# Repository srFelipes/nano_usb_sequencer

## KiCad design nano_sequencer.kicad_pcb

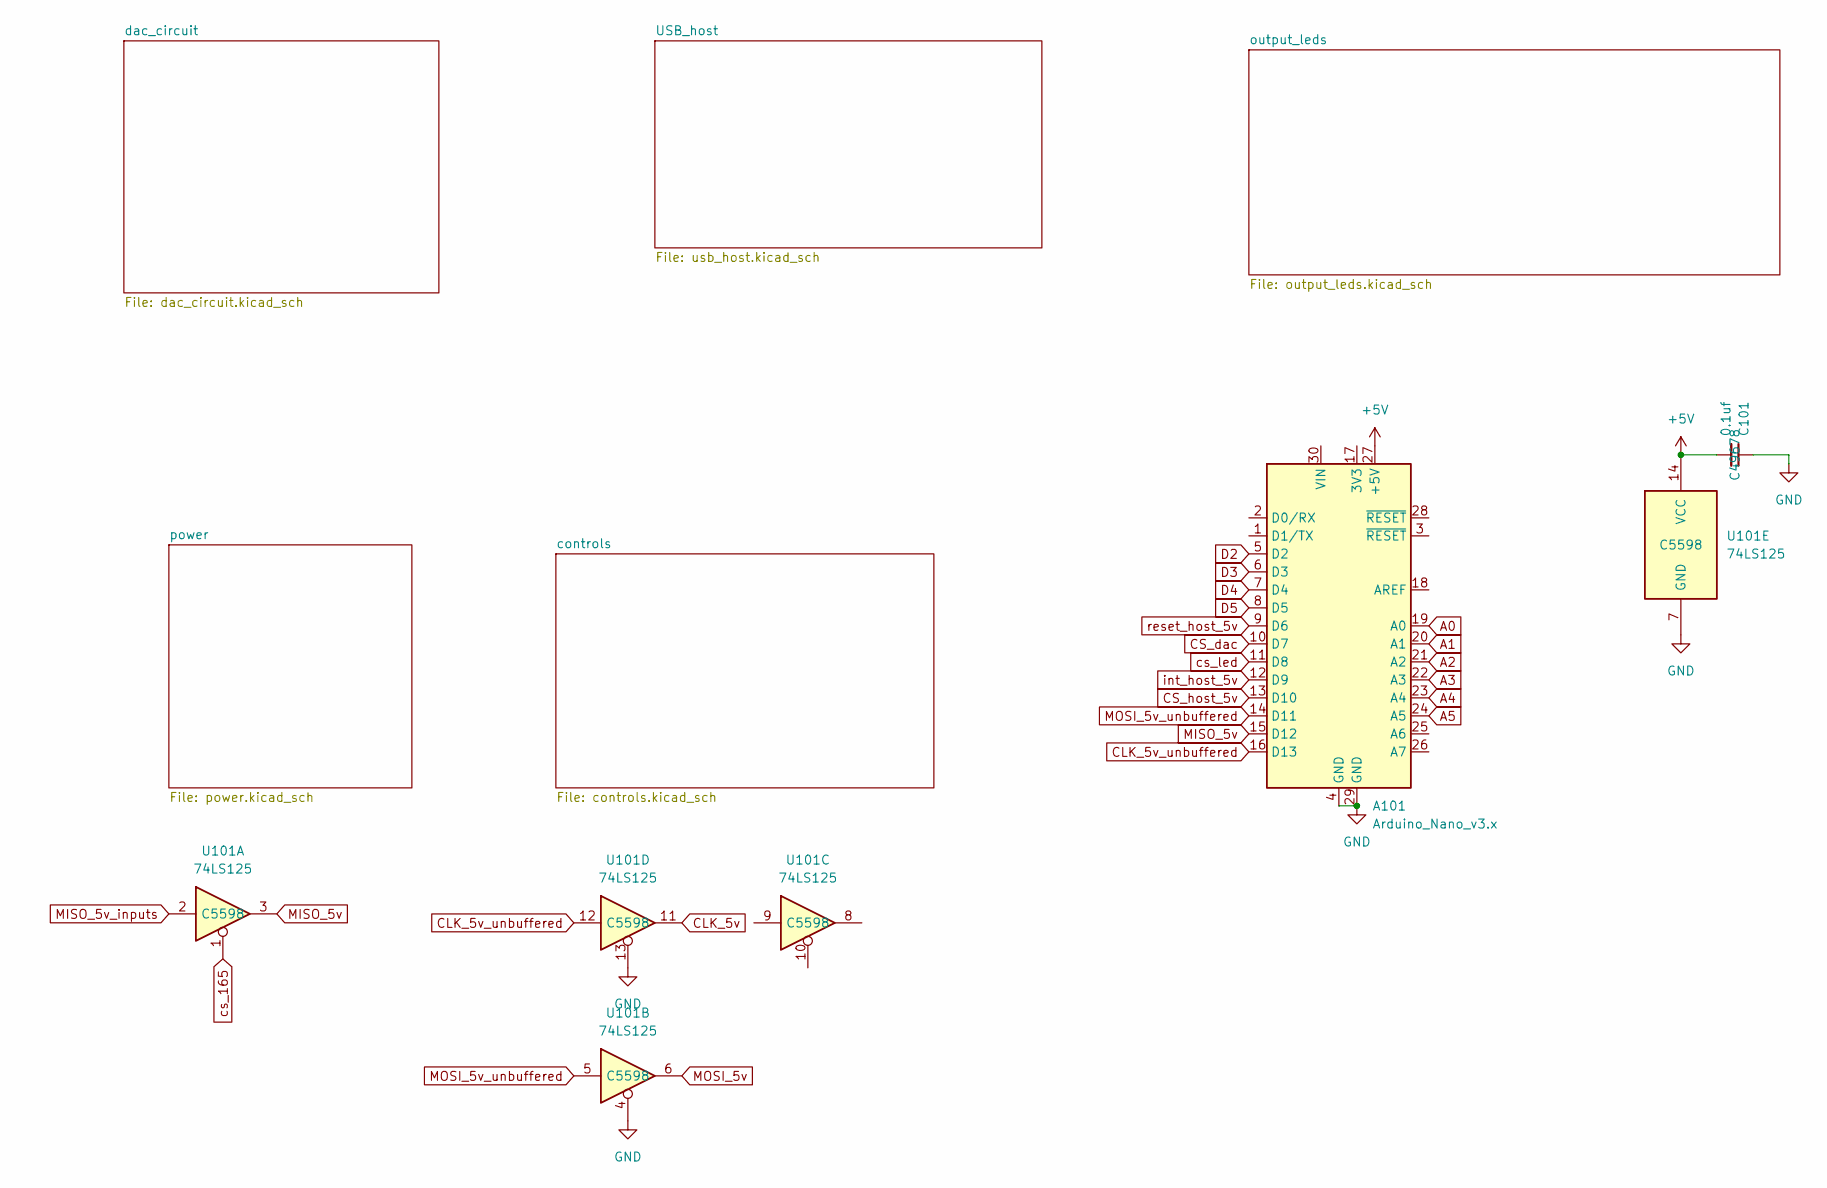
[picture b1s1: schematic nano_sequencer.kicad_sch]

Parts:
A101: Arduino_Nano_v3.x; Arduino_Nano
C101: 0.1uf; C_0805_2012Metric_Pad1.18x1.45mm_HandSolder; LCSC PN C49678
U101: 74LS125; SO-14_3.9x8.65mm_P1.27mm; LCSC PN C5598

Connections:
+5V: A101.27 (+5V), C101.2, U101.14 (VCC); also elsewhere on the board
A0: A101.19 (A0); also elsewhere on the board
A1: A101.20 (A1); also elsewhere on the board
A2: A101.21 (A2); also elsewhere on the board
A3: A101.22 (A3); also elsewhere on the board
A4: A101.23 (A4); also elsewhere on the board
A5: A101.24 (A5); also elsewhere on the board
CLK_5v: U101.11; also elsewhere on the board
CLK_5v_unbuffered: A101.16 (D13), U101.12
CS_dac: A101.10 (D7); also elsewhere on the board
CS_host_5v: A101.13 (D10); also elsewhere on the board
D2: A101.5 (D2); also elsewhere on the board
D3: A101.6 (D3); also elsewhere on the board
D4: A101.7 (D4); also elsewhere on the board
D5: A101.8 (D5); also elsewhere on the board
GND: A101.4 (GND), A101.29 (GND), C101.1, U101.4, U101.7 (GND), U101.13; also elsewhere on the board
MISO_5v: A101.15 (D12), U101.3; also elsewhere on the board
MISO_5v_inputs: U101.2; also elsewhere on the board
MOSI_5v: U101.6; also elsewhere on the board
MOSI_5v_unbuffered: A101.14 (D11), U101.5
cs_165: U101.1; also elsewhere on the board
cs_led: A101.11 (D8); also elsewhere on the board
int_host_5v: A101.12 (D9); also elsewhere on the board
reset_host_5v: A101.9 (D6); also elsewhere on the board

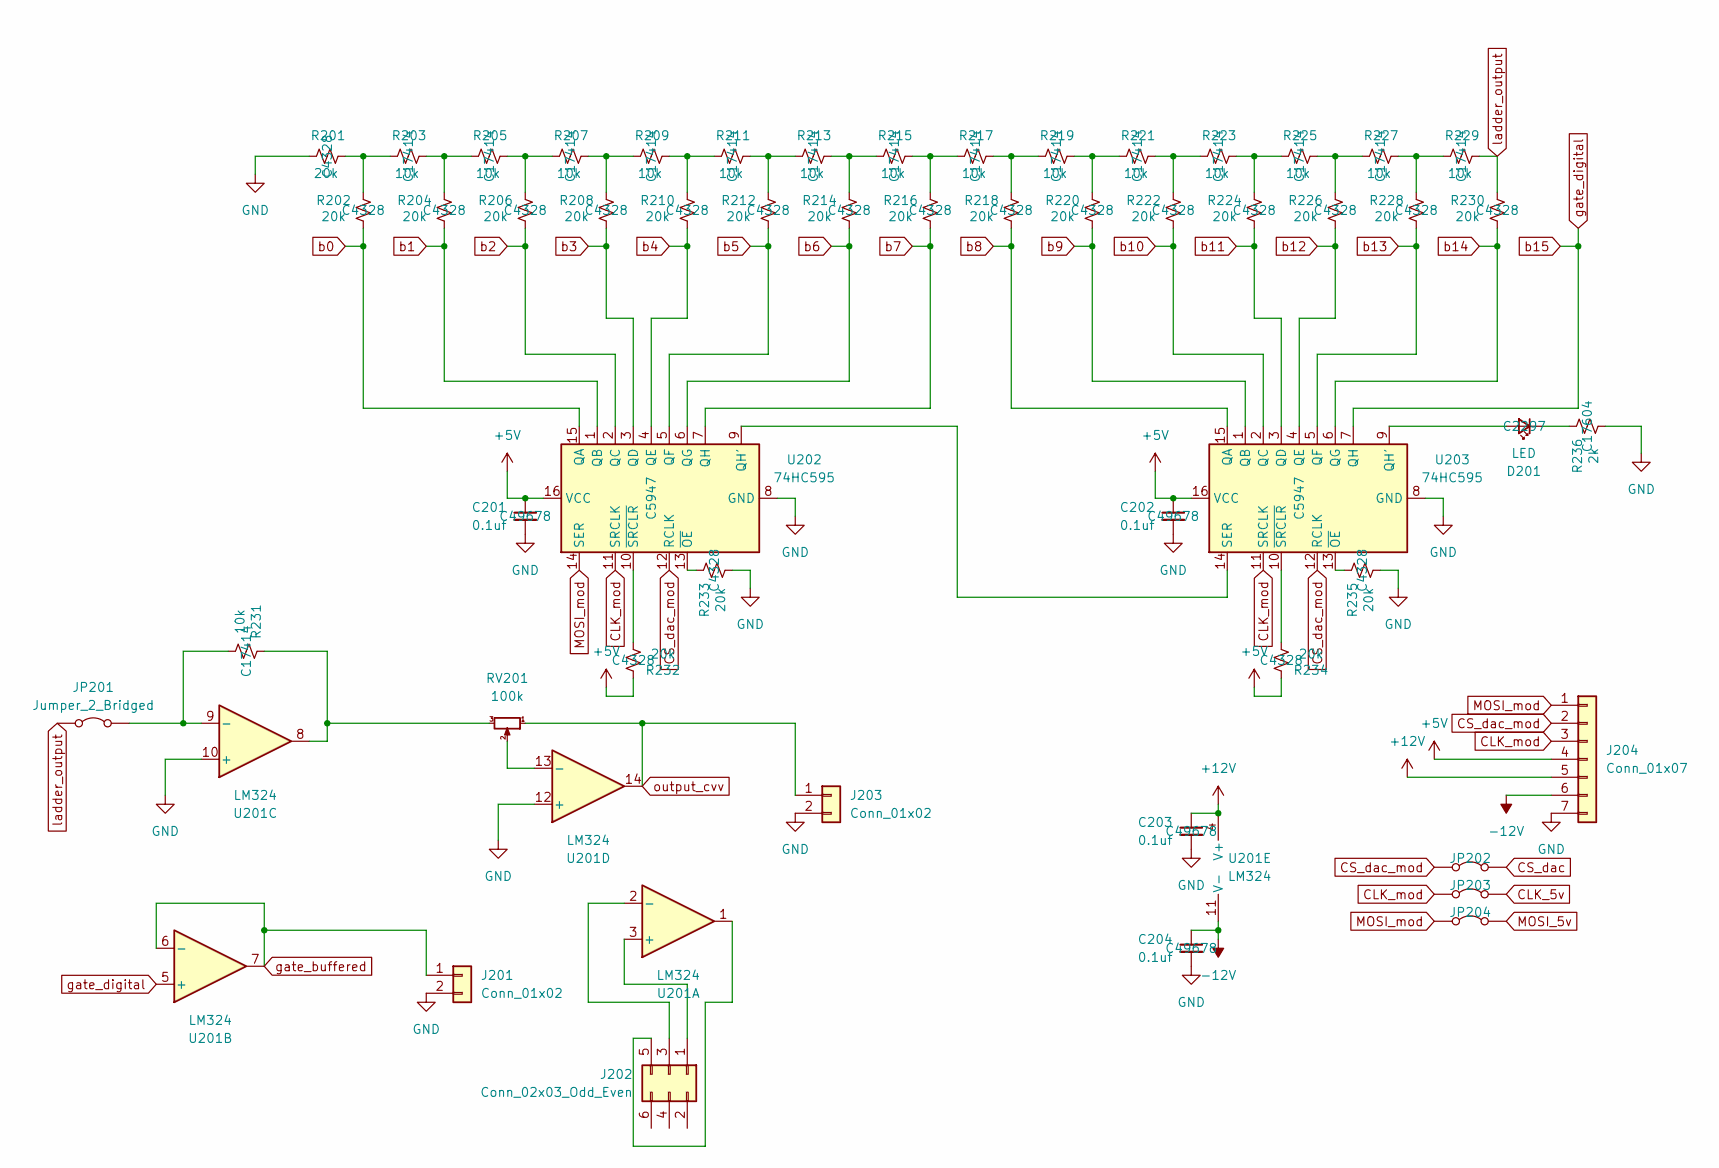
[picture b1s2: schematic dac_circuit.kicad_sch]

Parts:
C201, C202, C203, C204: 0.1uf; C_0805_2012Metric_Pad1.18x1.45mm_HandSolder; LCSC PN C49678
D201: LED; LED_0805_2012Metric_Pad1.15x1.40mm_HandSolder; LCSC PN C2297
J201, J203: Conn_01x02; PinHeader_1x02_P2.54mm_Vertical
J202: Conn_02x03_Odd_Even; PinHeader_2x03_P2.54mm_Vertical
J204: Conn_01x07; PinSocket_1x07_P2.54mm_Vertical
JP201: Jumper_2_Bridged; PinSocket_1x02_P2.54mm_Vertical
JP202, JP203, JP204: SolderJumper-2_P1.3mm_Bridged_RoundedPad1.0x1.5mm
R201, R202, R204, R206, R208, R210, R212, R214, R216, R218, R220, R222, R224, R226, R228, R230, R232, R233, R234, R235: 20k; R_0805_2012Metric_Pad1.20x1.40mm_HandSolder; LCSC PN C4328
R203, R205, R207, R209, R211, R213, R215, R217, R219, R221, R223, R225, R227, R229, R231: 10k; R_0805_2012Metric_Pad1.20x1.40mm_HandSolder; LCSC PN C17414
R236: 2k; R_0805_2012Metric_Pad1.20x1.40mm_HandSolder; LCSC PN C17604
RV201: 100k; Potentiometer_Bourns_3296W_Vertical
U201: LM324; CERDIP-14_W7.62mm_SideBrazed_LongPads
U202, U203: 74HC595; SO-16_3.9x9.9mm_P1.27mm; LCSC PN C5947

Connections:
+5V: C201.1, C202.1, J204.4, R232.2, R234.2, U202.16 (VCC), U203.16 (VCC); also elsewhere on the board
+12V: C203.1, J204.5, U201.4 (V+); also elsewhere on the board
-12V: C204.1, J204.6, U201.11 (V-); also elsewhere on the board
CLK_5v: JP203.2 (B); also elsewhere on the board
CLK_mod: J204.3, JP203.1 (A), U202.11 (SRCLK), U203.11 (SRCLK)
CS_dac: JP202.2 (B); also elsewhere on the board
CS_dac_mod: J204.2, JP202.1 (A), U202.12 (RCLK), U203.12 (RCLK)
GND: C201.2, C202.2, C203.2, C204.2, J201.2, J203.2, J204.7, R201.1, R233.1, R235.1, R236.1, U201.10 (+), U201.12 (+), U202.8 (GND), U203.8 (GND); also elsewhere on the board
MOSI_5v: JP204.2 (B); also elsewhere on the board
MOSI_mod: J204.1, JP204.1 (A), U202.14 (SER)
unnamed: D201.2 (A), U203.9 (QH')
unnamed: D201.1 (K), R236.2
unnamed: J202.1, U201.3 (+)
unnamed: J202.3, U201.2 (-)
unnamed: J202.5, U201.1
unnamed: JP201.2 (B), R231.1, U201.9 (-)
unnamed: R201.2, R202.2, R203.1
unnamed: R203.2, R204.2, R205.1
unnamed: R205.2, R206.2, R207.1
unnamed: R207.2, R208.2, R209.1
unnamed: R209.2, R210.2, R211.1
unnamed: R211.2, R212.2, R213.1
unnamed: R213.2, R214.2, R215.1
unnamed: R215.2, R216.2, R217.1
unnamed: R217.2, R218.2, R219.1
unnamed: R219.2, R220.2, R221.1
unnamed: R221.2, R222.2, R223.1
unnamed: R223.2, R224.2, R225.1
unnamed: R225.2, R226.2, R227.1
unnamed: R227.2, R228.2, R229.1
unnamed: R231.2, RV201.3, U201.8
unnamed: RV201.2, U201.13 (-)
unnamed: U202.9 (QH'), U203.14 (SER)
unnamed: R233.2, U202.13 (~OE)
unnamed: R232.1, U202.10 (~SRCLR)
unnamed: R235.2, U203.13 (~OE)
unnamed: R234.1, U203.10 (~SRCLR)
b0: R202.1, U202.15 (QA)
b1: R204.1, U202.1 (QB)
b2: R206.1, U202.2 (QC)
b3: R208.1, U202.3 (QD)
b4: R210.1, U202.4 (QE)
b5: R212.1, U202.5 (QF)
b6: R214.1, U202.6 (QG)
b7: R216.1, U202.7 (QH)
b8: R218.1, U203.15 (QA)
b9: R220.1, U203.1 (QB)
b10: R222.1, U203.2 (QC)
b11: R224.1, U203.3 (QD)
b12: R226.1, U203.4 (QE)
b13: R228.1, U203.5 (QF)
b14: R230.1, U203.6 (QG)
b15: U201.5 (+), U203.7 (QH)
gate_buffered: J201.1, U201.6 (-), U201.7
ladder_output: JP201.1 (A), R229.2, R230.2
output_cvv: J203.1, RV201.1, U201.14

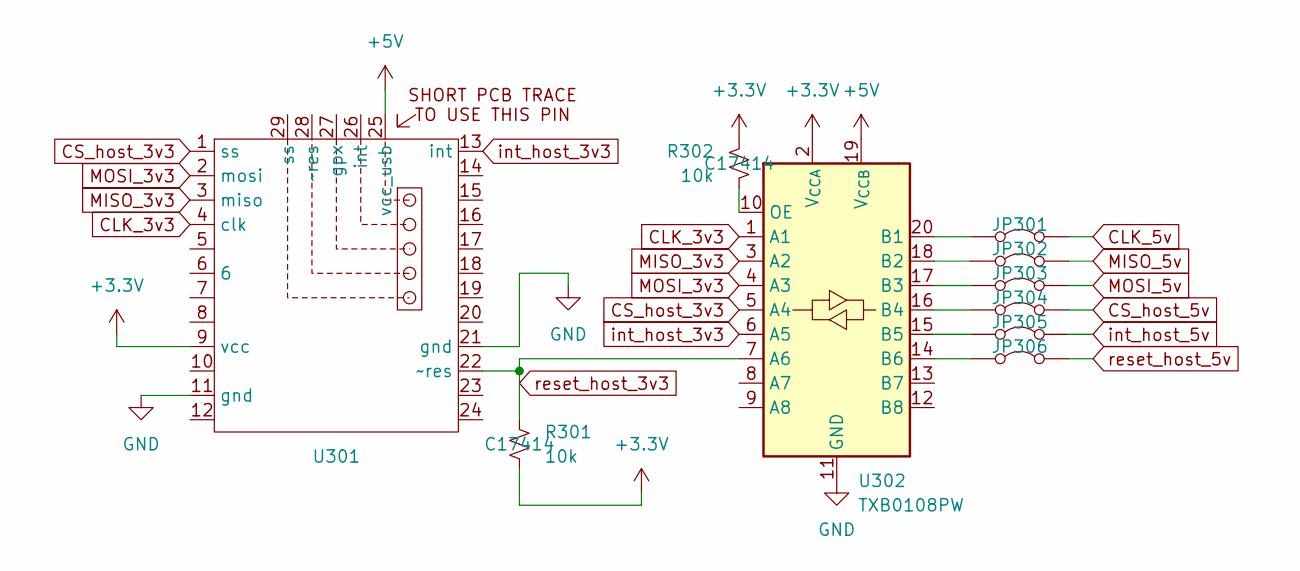
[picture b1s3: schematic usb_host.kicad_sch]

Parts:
JP301, JP302, JP303, JP304, JP305, JP306: SolderJumper-2_P1.3mm_Bridged_RoundedPad1.0x1.5mm
R301, R302: 10k; R_0805_2012Metric_Pad1.20x1.40mm_HandSolder; LCSC PN C17414
U301: max3421_ali_board
U302: TXB0108PW; TXS0108E_pcb_module

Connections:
+3.3V: R301.1, R302.1, U301.9 (vcc), U302.2 (V_{CCA}); also elsewhere on the board
+5V: U301.25 (vcc_usb), U302.19 (V_{CCB}); also elsewhere on the board
CLK_3v3: U301.4 (clk), U302.1 (A1)
CLK_5v: JP301.2 (B); also elsewhere on the board
CS_host_3v3: U301.1 (ss), U302.5 (A4)
CS_host_5v: JP304.2 (B); also elsewhere on the board
GND: U301.11 (gnd), U301.21 (gnd), U302.11 (GND); also elsewhere on the board
MISO_3v3: U301.3 (miso), U302.3 (A2)
MISO_5v: JP302.2 (B); also elsewhere on the board
MOSI_3v3: U301.2 (mosi), U302.4 (A3)
MOSI_5v: JP303.2 (B); also elsewhere on the board
unnamed: JP301.1 (A), U302.20 (B1)
unnamed: JP302.1 (A), U302.18 (B2)
unnamed: JP303.1 (A), U302.17 (B3)
unnamed: JP304.1 (A), U302.16 (B4)
unnamed: JP305.1 (A), U302.15 (B5)
unnamed: JP306.1 (A), U302.14 (B6)
unnamed: R302.2, U302.10 (OE)
int_host_3v3: U301.13 (int), U302.6 (A5)
int_host_5v: JP305.2 (B); also elsewhere on the board
reset_host_3v3: R301.2, U301.22 (~res), U302.7 (A6)
reset_host_5v: JP306.2 (B); also elsewhere on the board

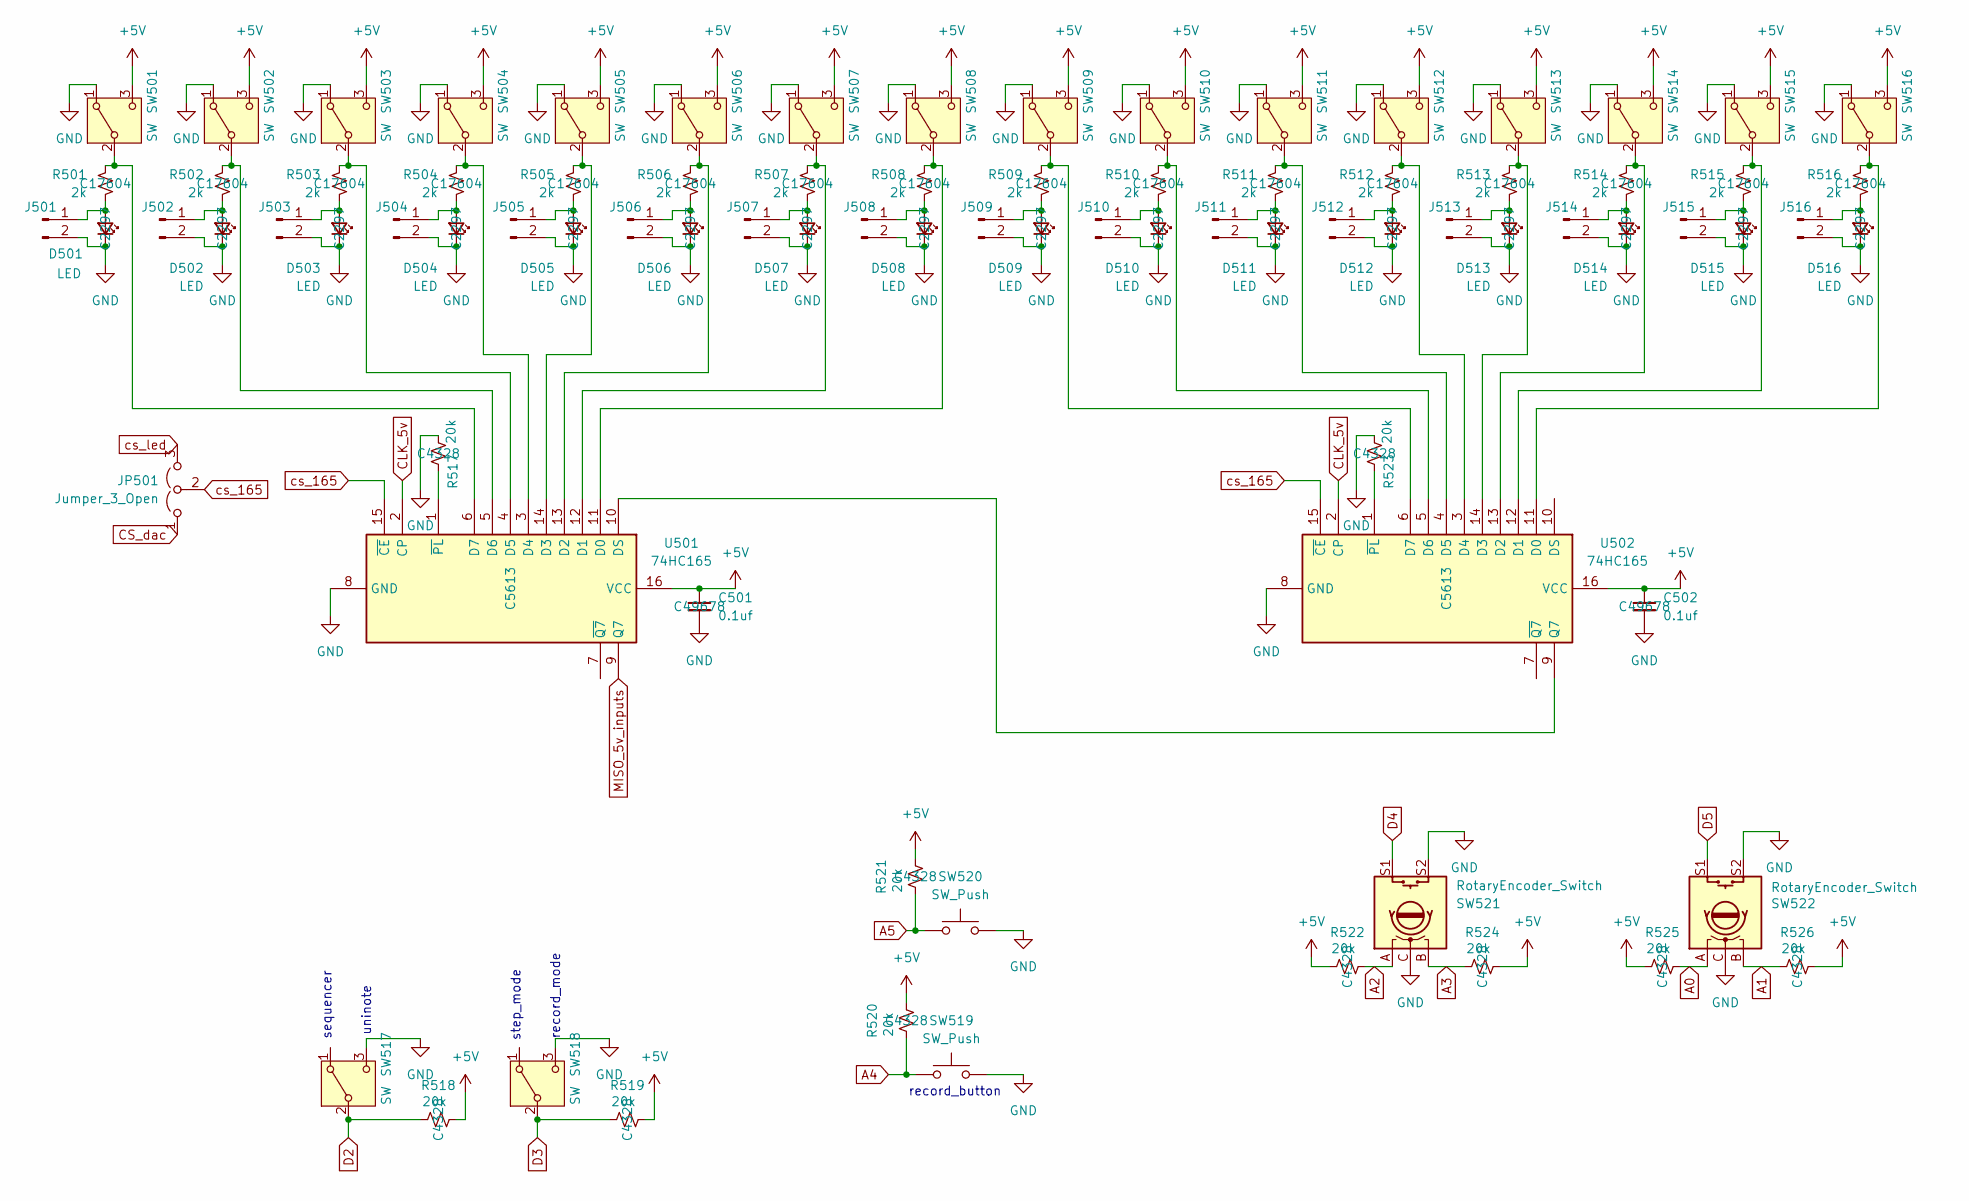
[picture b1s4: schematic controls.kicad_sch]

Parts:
C501, C502: 0.1uf; C_0805_2012Metric_Pad1.18x1.45mm_HandSolder; LCSC PN C49678
D501, D502, D503, D504, D505, D506, D507, D508, D509, D510, D511, D512, D513, D514, D515, D516: LED; LED_0805_2012Metric_Pad1.15x1.40mm_HandSolder; LCSC PN C2297
J501, J502, J503, J504, J505, J506, J507, J508, J509, J510, J511, J512, J513, J514, J515, J516: Conn_01x02_Pin; PinSocket_1x02_P2.54mm_Vertical
JP501: Jumper_3_Open; PinHeader_1x03_P2.54mm_Vertical
R501, R502, R503, R504, R505, R506, R507, R508, R509, R510, R511, R512, R513, R514, R515, R516: 2k; R_0805_2012Metric_Pad1.20x1.40mm_HandSolder; LCSC PN C17604
R517, R518, R519, R520, R521, R522, R523, R524, R525, R526: 20k; R_0805_2012Metric_Pad1.20x1.40mm_HandSolder; LCSC PN C4328
SW501, SW502, SW503, SW504, SW505, SW506, SW507, SW508, SW509, SW510, SW511, SW512, SW513, SW514, SW515, SW516, SW517, SW518: SW; PinSocket_1x03_P2.54mm_Vertical
SW519, SW520: SW_Push; PinSocket_1x02_P2.54mm_Vertical
SW521, SW522: RotaryEncoder_Switch; RotaryEncoder_Alps_EC11E-Switch_Vertical_H20mm
U501, U502: 74HC165; SO-16_3.9x9.9mm_P1.27mm; LCSC PN C5613

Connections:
+5V: C501.1, C502.1, R518.2, R519.2, R520.2, R521.2, R522.1, R524.2, R525.1, R526.2, SW501.3 (C), SW502.3 (C), SW503.3 (C), SW504.3 (C), SW505.3 (C), SW506.3 (C), SW507.3 (C), SW508.3 (C), SW509.3 (C), SW510.3 (C), SW511.3 (C), SW512.3 (C), SW513.3 (C), SW514.3 (C), SW515.3 (C), SW516.3 (C), U501.16 (VCC), U502.16 (VCC); also elsewhere on the board
A0: R525.2, SW522.A; also elsewhere on the board
A1: R526.1, SW522.B; also elsewhere on the board
A2: R522.2, SW521.A; also elsewhere on the board
A3: R524.1, SW521.B; also elsewhere on the board
A4: R520.1, SW519.1; also elsewhere on the board
A5: R521.1, SW520.1; also elsewhere on the board
CLK_5v: U501.2 (CP), U502.2 (CP); also elsewhere on the board
CS_dac: JP501.1 (A); also elsewhere on the board
D2: R518.1, SW517.2 (B); also elsewhere on the board
D3: R519.1, SW518.2 (B); also elsewhere on the board
D4: SW521.S1; also elsewhere on the board
D5: SW522.S1; also elsewhere on the board
GND: C501.2, C502.2, D501.1 (K), D502.1 (K), D503.1 (K), D504.1 (K), D505.1 (K), D506.1 (K), D507.1 (K), D508.1 (K), D509.1 (K), D510.1 (K), D511.1 (K), D512.1 (K), D513.1 (K), D514.1 (K), D515.1 (K), D516.1 (K), J501.2, J502.2, J503.2, J504.2, J505.2, J506.2, J507.2, J508.2, J509.2, J510.2, J511.2, J512.2, J513.2, J514.2, J515.2, J516.2, R517.1, R523.1, SW501.1 (A), SW502.1 (A), SW503.1 (A), SW504.1 (A), SW505.1 (A), SW506.1 (A), SW507.1 (A), SW508.1 (A), SW509.1 (A), SW510.1 (A), SW511.1 (A), SW512.1 (A), SW513.1 (A), SW514.1 (A), SW515.1 (A), SW516.1 (A), SW517.3 (C), SW518.3 (C), SW519.2, SW520.2, SW521.C, SW521.S2, SW522.C, SW522.S2, U501.8 (GND), U502.8 (GND); also elsewhere on the board
MISO_5v_inputs: U501.9 (Q7); also elsewhere on the board
unnamed: D501.2 (A), J501.1, R501.2
unnamed: D502.2 (A), J502.1, R502.2
unnamed: D503.2 (A), J503.1, R503.2
unnamed: D504.2 (A), J504.1, R504.2
unnamed: D505.2 (A), J505.1, R505.2
unnamed: D506.2 (A), J506.1, R506.2
unnamed: D507.2 (A), J507.1, R507.2
unnamed: D508.2 (A), J508.1, R508.2
unnamed: D509.2 (A), J509.1, R509.2
unnamed: D510.2 (A), J510.1, R510.2
unnamed: D511.2 (A), J511.1, R511.2
unnamed: D512.2 (A), J512.1, R512.2
unnamed: D513.2 (A), J513.1, R513.2
unnamed: D514.2 (A), J514.1, R514.2
unnamed: D515.2 (A), J515.1, R515.2
unnamed: D516.2 (A), J516.1, R516.2
unnamed: R501.1, SW501.2 (B), U501.6 (D7)
unnamed: R502.1, SW502.2 (B), U501.5 (D6)
unnamed: R503.1, SW503.2 (B), U501.4 (D5)
unnamed: R504.1, SW504.2 (B), U501.3 (D4)
unnamed: R505.1, SW505.2 (B), U501.14 (D3)
unnamed: R506.1, SW506.2 (B), U501.13 (D2)
unnamed: R507.1, SW507.2 (B), U501.12 (D1)
unnamed: R508.1, SW508.2 (B), U501.11 (D0)
unnamed: R509.1, SW509.2 (B), U502.6 (D7)
unnamed: R510.1, SW510.2 (B), U502.5 (D6)
unnamed: R511.1, SW511.2 (B), U502.4 (D5)
unnamed: R512.1, SW512.2 (B), U502.3 (D4)
unnamed: R513.1, SW513.2 (B), U502.14 (D3)
unnamed: R514.1, SW514.2 (B), U502.13 (D2)
unnamed: R515.1, SW515.2 (B), U502.12 (D1)
unnamed: R516.1, SW516.2 (B), U502.11 (D0)
unnamed: U501.10 (DS), U502.9 (Q7)
unnamed: R517.2, U501.1 (~PL)
unnamed: R523.2, U502.1 (~PL)
cs_165: JP501.2 (C), U501.15 (~CE), U502.15 (~CE); also elsewhere on the board
cs_led: JP501.3 (B); also elsewhere on the board

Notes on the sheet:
record_mode
uninote
step_mode
record_button
sequencer

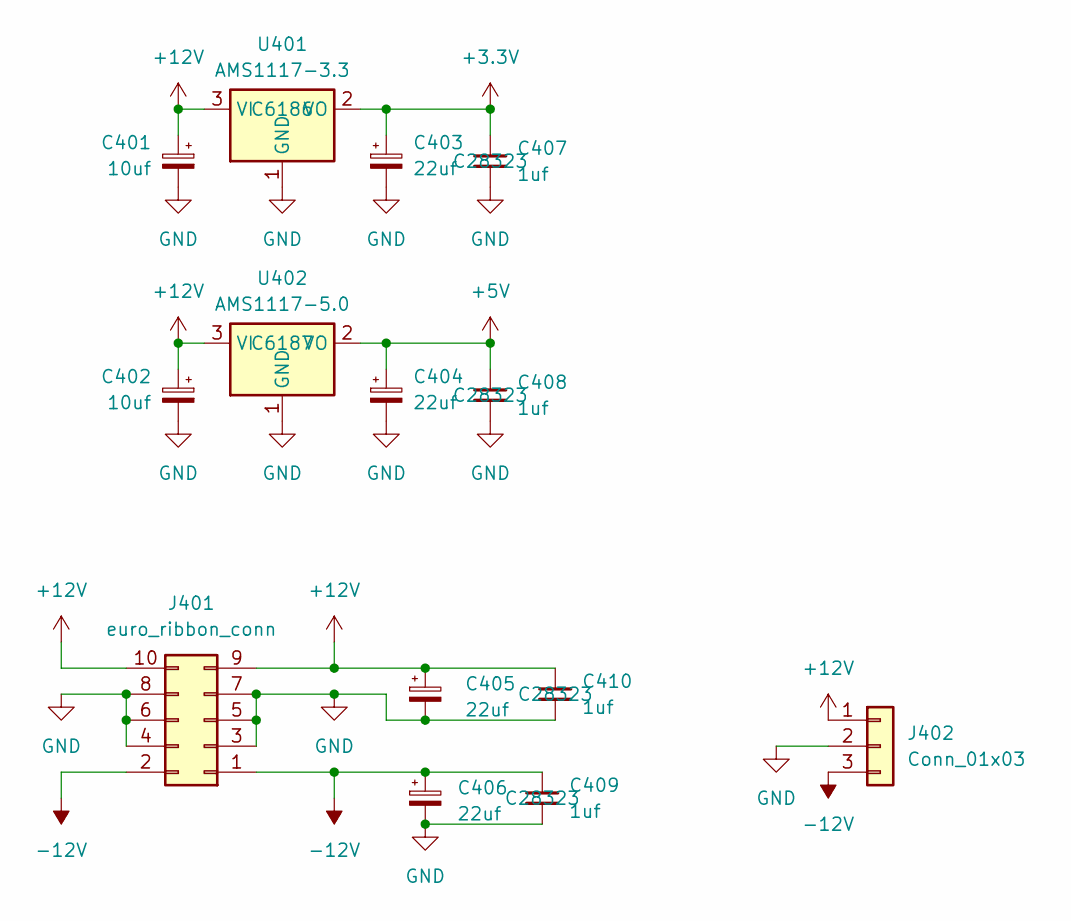
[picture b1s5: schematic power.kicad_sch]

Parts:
C401, C402: 10uf; CP_Radial_Tantal_D4.5mm_P2.50mm
C403, C404: 22uf; CP_Radial_Tantal_D4.5mm_P2.50mm
C405, C406: 22uf; CP_Radial_D6.3mm_P2.50mm
C407, C408, C409, C410: 1uf; C_0805_2012Metric_Pad1.18x1.45mm_HandSolder; LCSC PN C28323
J401: euro_ribbon_conn; IDC-Header_2x05_P2.54mm_Vertical
J402: Conn_01x03; JST_EH_B3B-EH-A_1x03_P2.50mm_Vertical
U401: AMS1117-3.3; SOT-223-3_TabPin2; LCSC PN C6186
U402: AMS1117-5.0; SOT-223-3_TabPin2; LCSC PN C6187

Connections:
+3.3V: C403.1, C407.1, U401.2 (VO); also elsewhere on the board
+5V: C404.1, C408.1, U402.2 (VO); also elsewhere on the board
+12V: C401.1, C402.1, C405.1, C410.1, J401.9, J401.10, J402.1, U401.3 (VI), U402.3 (VI); also elsewhere on the board
-12V: C406.1, C409.1, J401.1, J401.2, J402.3; also elsewhere on the board
GND: C401.2, C402.2, C403.2, C404.2, C405.2, C406.2, C407.2, C408.2, C409.2, C410.2, J401.3, J401.4, J401.5, J401.6, J401.7, J401.8, J402.2, U401.1 (GND), U402.1 (GND); also elsewhere on the board

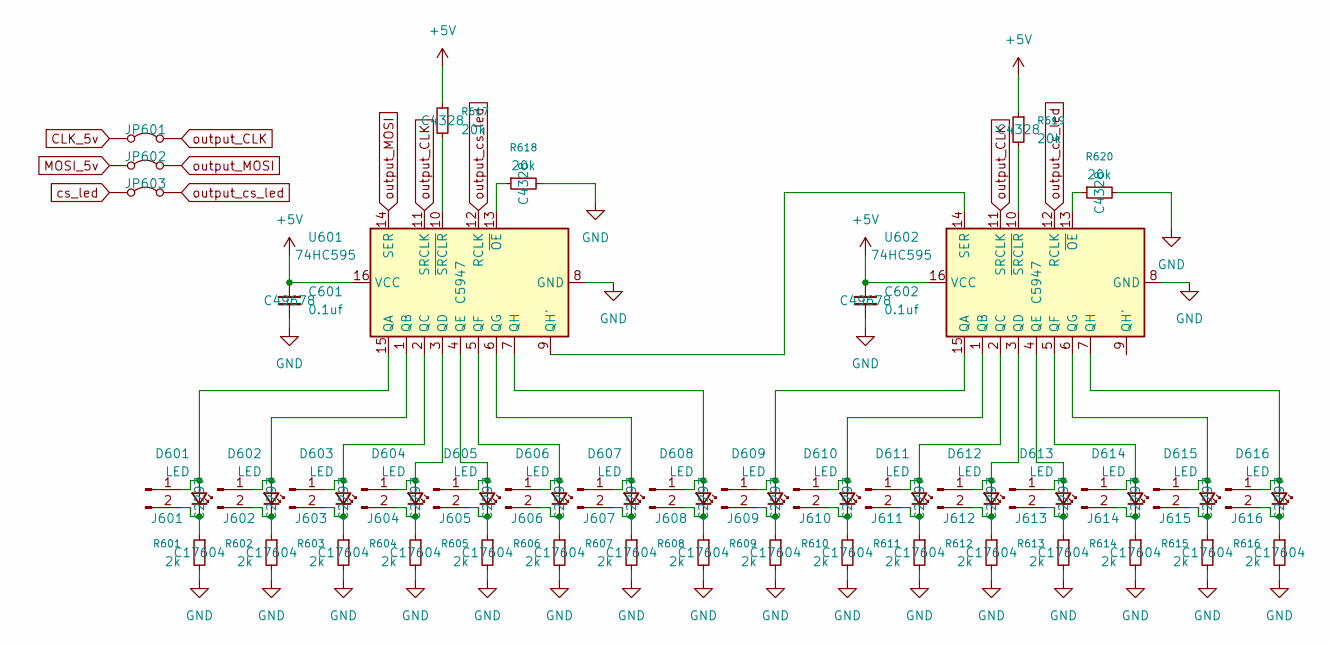
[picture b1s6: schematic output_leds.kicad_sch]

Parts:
C601, C602: 0.1uf; C_0805_2012Metric_Pad1.18x1.45mm_HandSolder; LCSC PN C49678
D601, D602, D603, D604, D605, D606, D607, D608, D609, D610, D611, D612, D613, D614, D615, D616: LED; LED_0805_2012Metric_Pad1.15x1.40mm_HandSolder; LCSC PN C2297
J601, J602, J603, J604, J605, J606, J607, J608, J609, J610, J611, J612, J613, J614, J615, J616: Conn_01x02_Pin; PinSocket_1x02_P2.54mm_Vertical
JP601, JP602, JP603: SolderJumper-2_P1.3mm_Bridged_RoundedPad1.0x1.5mm
R601, R602, R603, R604, R605, R606, R607, R608, R609, R610, R611, R612, R613, R614, R615, R616: 2k; R_0805_2012Metric_Pad1.20x1.40mm_HandSolder; LCSC PN C17604
R617, R618, R619, R620: 20k; R_0805_2012Metric_Pad1.20x1.40mm_HandSolder; LCSC PN C4328
U601, U602: 74HC595; SO-16_3.9x9.9mm_P1.27mm; LCSC PN C5947

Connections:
+5V: C601.1, C602.1, R617.1, R619.1, U601.16 (VCC), U602.16 (VCC); also elsewhere on the board
CLK_5v: JP601.1 (A); also elsewhere on the board
GND: C601.2, C602.2, R601.2, R602.2, R603.2, R604.2, R605.2, R606.2, R607.2, R608.2, R609.2, R610.2, R611.2, R612.2, R613.2, R614.2, R615.2, R616.2, R618.2, R620.2, U601.8 (GND), U602.8 (GND); also elsewhere on the board
MOSI_5v: JP602.1 (A); also elsewhere on the board
unnamed: D601.2 (A), J601.1, U601.15 (QA)
unnamed: D601.1 (K), J601.2, R601.1
unnamed: D602.2 (A), J602.1, U601.1 (QB)
unnamed: D602.1 (K), J602.2, R602.1
unnamed: D603.2 (A), J603.1, U601.2 (QC)
unnamed: D603.1 (K), J603.2, R603.1
unnamed: D604.2 (A), J604.1, U601.3 (QD)
unnamed: D604.1 (K), J604.2, R604.1
unnamed: D605.2 (A), J605.1, U601.4 (QE)
unnamed: D605.1 (K), J605.2, R605.1
unnamed: D606.2 (A), J606.1, U601.5 (QF)
unnamed: D606.1 (K), J606.2, R606.1
unnamed: D607.2 (A), J607.1, U601.6 (QG)
unnamed: D607.1 (K), J607.2, R607.1
unnamed: D608.2 (A), J608.1, U601.7 (QH)
unnamed: D608.1 (K), J608.2, R608.1
unnamed: D609.2 (A), J609.1, U602.15 (QA)
unnamed: D609.1 (K), J609.2, R609.1
unnamed: D610.2 (A), J610.1, U602.1 (QB)
unnamed: D610.1 (K), J610.2, R610.1
unnamed: D611.2 (A), J611.1, U602.2 (QC)
unnamed: D611.1 (K), J611.2, R611.1
unnamed: D612.2 (A), J612.1, U602.3 (QD)
unnamed: D612.1 (K), J612.2, R612.1
unnamed: D613.2 (A), J613.1, U602.4 (QE)
unnamed: D613.1 (K), J613.2, R613.1
unnamed: D614.2 (A), J614.1, U602.5 (QF)
unnamed: D614.1 (K), J614.2, R614.1
unnamed: D615.2 (A), J615.1, U602.6 (QG)
unnamed: D615.1 (K), J615.2, R615.1
unnamed: D616.2 (A), J616.1, U602.7 (QH)
unnamed: D616.1 (K), J616.2, R616.1
unnamed: U601.9 (QH'), U602.14 (SER)
unnamed: R618.1, U601.13 (~OE)
unnamed: R617.2, U601.10 (~SRCLR)
unnamed: R620.1, U602.13 (~OE)
unnamed: R619.2, U602.10 (~SRCLR)
cs_led: JP603.1 (A); also elsewhere on the board
output_CLK: JP601.2 (B), U601.11 (SRCLK), U602.11 (SRCLK)
output_MOSI: JP602.2 (B), U601.14 (SER)
output_cs_led: JP603.2 (B), U601.12 (RCLK), U602.12 (RCLK)

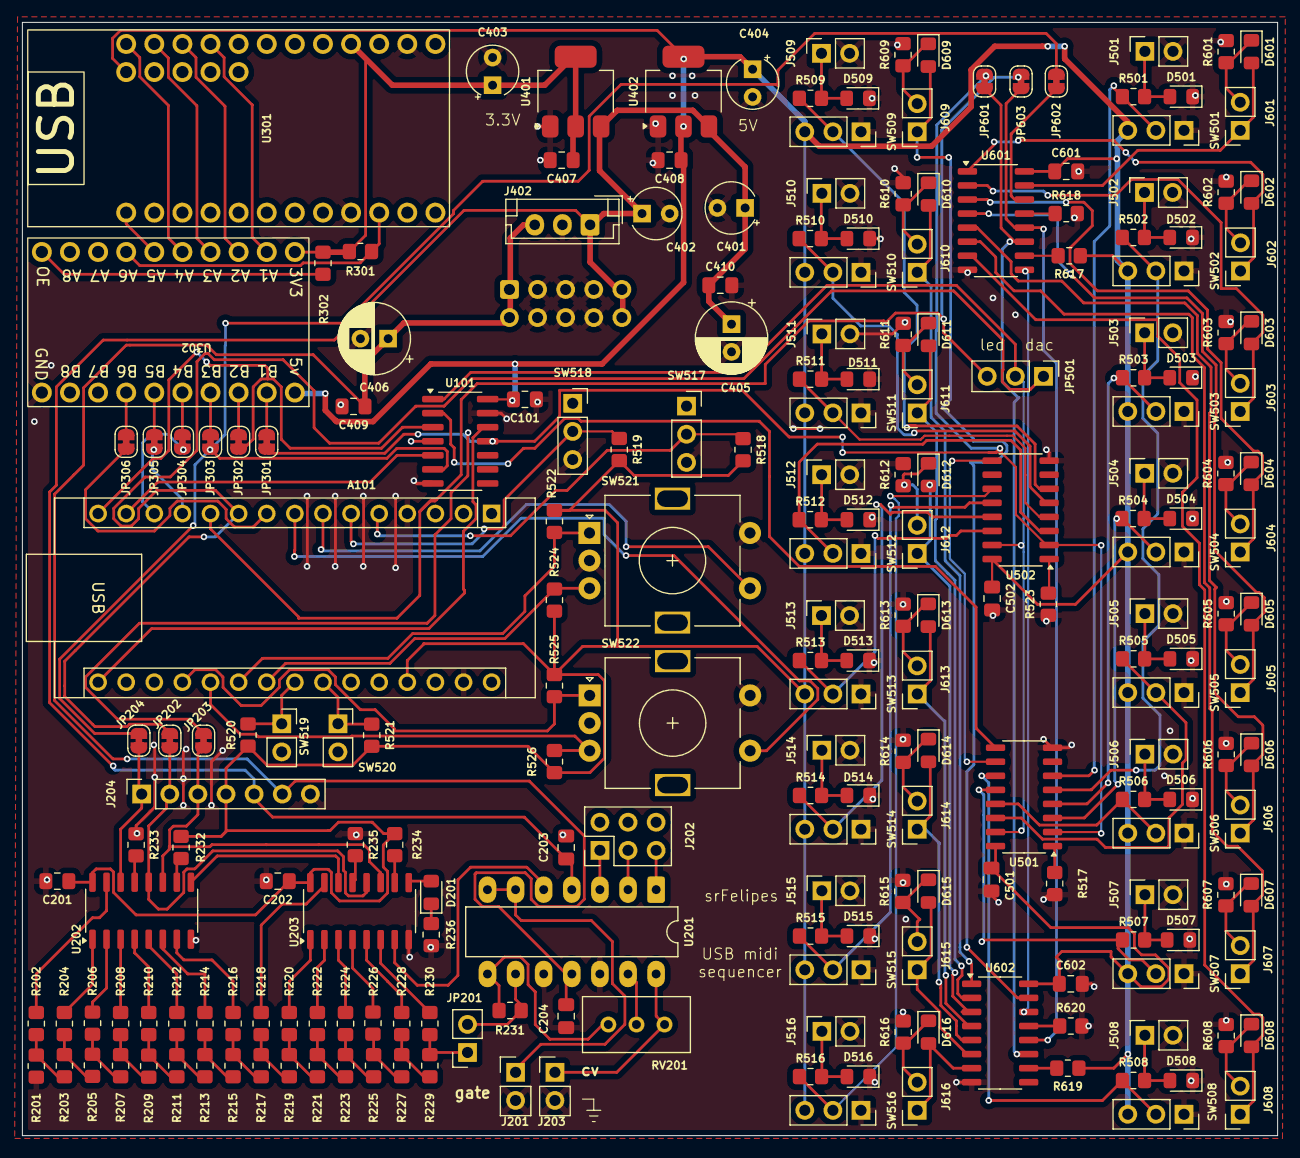
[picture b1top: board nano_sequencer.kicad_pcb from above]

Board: 2 copper layers, 113.4 x 100.6 mm, 224 parts (1 on the bottom side), 164 nets.

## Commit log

2025-04-11 base version
2025-04-11 added custom symbols libraries and footprints
2025-04-11 Create fp-lib-table
    footprints are now local
2025-04-14 schematic done, routed dac ladder
2025-04-15 grouped components in board
2025-04-17 routed half of inputs mess
2025-04-17 routing spi traces (most of them) and a quarter of the input mess
2025-04-24 FINISHED ROUTING
2025-04-24 added lcsc part numbers and fabrication files
